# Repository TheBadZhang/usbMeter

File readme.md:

# usbMeter

简易 usb 电流表，精度 1mA，支持正负 4.0A 电流测量。

## 实物

## 更新注记

### V1.0.0

实现了最基础的电压、电流、功率的读取和显示

### V0.0.1

这个版本是最初的版本，具有我能够塞入的所有功能，结果发现嘉立创免费打样只支持0.3mm的孔，导致没有办法低价进行生产，随放弃，删除大量功能，只保留了最基本的功能，做出了 V1.0.0 版本

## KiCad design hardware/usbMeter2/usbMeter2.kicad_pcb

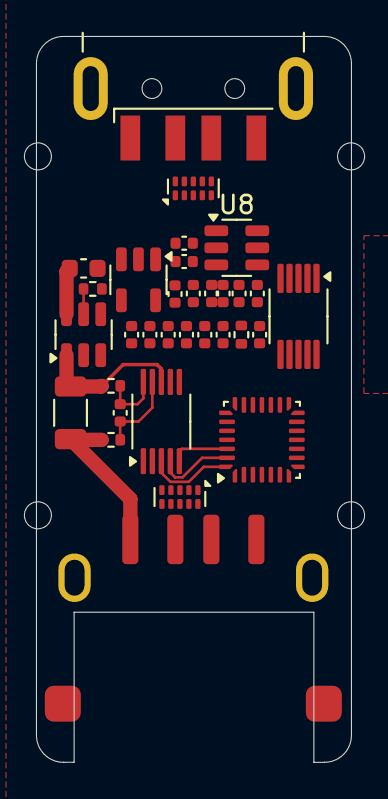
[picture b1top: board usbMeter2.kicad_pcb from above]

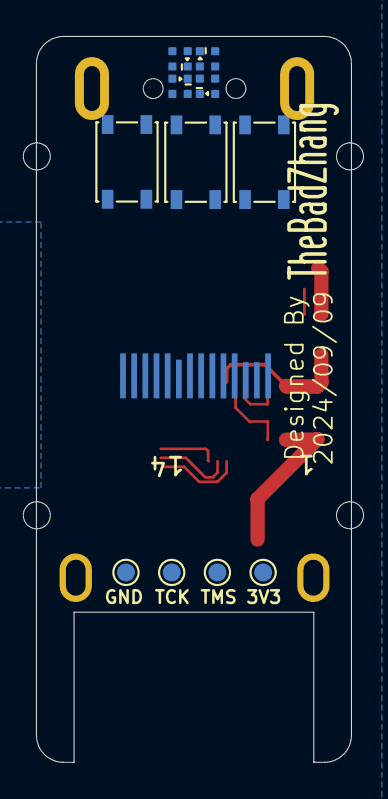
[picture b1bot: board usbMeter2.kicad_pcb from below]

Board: 2 copper layers, 17.5 x 40.3 mm, 48 parts (12 on the bottom side), 44 nets.

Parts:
C1, C20: 2.2uF; C_0402_1005Metric
C2, C5: 100nF; C_0402_1005Metric
C3, C4, C8, C18, C22: 0.1uF; C_0402_1005Metric
C6: 10uF; C_0603_1608Metric
C7, C10, C19, C21: 4.7uF; C_0402_1005Metric
C9: 22nF; C_0402_1005Metric
C16, C17: 1uF; C_0402_1005Metric
D1, D2, D3, D4: WS2812B-2020; ws2812-1010
H1, H2, H3, H4: MountingHole; mountinghold_nopad_m1.4
J1: USB_A; USB_A_CNCTech_1001-011-01101_Horizontal
J2: USB_A; C2763021
R3, R5: 68R; R_0402_1005Metric
R4: 20mR; R_1206_3216Metric
R6: 100k; R_0402_1005Metric
R12: 560K; R_0402_1005Metric
SW1, SW2, SW3: SW_Push; KEY-SMD_4P-L4.2-W3.4-P2.15-LS4.5-TL
TP1, TP2, TP3, TP4: TestPoint; TestPoint_Pad_D1.0mm
U1: STM32G031G8Ux; QFN-28_4x4mm_P0.5mm
U2, U3: TPD4E05U06DQA; USON-10_2.5x1.0mm_P0.5mm
U4: CH340E; MSOP-10_3x3mm_P0.5mm
U5: INA228; VSSOP-10_3x3mm_P0.5mm
U6: CH217K; TSOT-23-6
U7: RT9193-33GB; SOT-23-5
U8: TPS54202DDC; SOT-23-6
U9: iic_oled_12864_ssd1312_2

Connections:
+3V3: C1.1, C2.1, C3.1, C4.1, C10.2, C18.1, C19.1, TP3.1, U1.3 (VDD), U4.7 (VCC), U4.10 (V3), U5.6 (VS), U7.5 (Vout), U9.5 (VBAT), U9.8 (VDD)
+5V: C7.1, C8.1, U7.1 (Vin), U7.3 (EN)
/CH217_FLAG: U1.14 (PB0), U6.3 (FLAG#)
/D2+: J1.3 (D+), U3.4 (D2+), U3.7 (NC), U4.1 (UD+)
/D2-: J1.2 (D-), U3.2 (D1-), U3.9 (NC), U4.2 (UD-)
/D+: J2.3 (D+), U2.4 (D2+), U2.7 (NC)
/D-: J2.2 (D-), U2.5 (D2-), U2.6 (NC)
/KEY1: SW1.2, U1.23 (PB3)
/KEY2: SW2.2, U1.24 (PB4)
/NRST: SW3.2, U1.5 (PF2)
/OLED_RST: U1.22 (PA15), U9.9 (RES#)
/SCL1: U1.26 (PB6), U5.5 (SCL)
/SCL2: U1.18 (PA11/PA9), U9.10 (SCL)
/SDA1: U1.27 (PB7), U5.4 (SDA)
/SDA2: U1.19 (PA12/PA10), U9.11 (SDA)
/SYS_SWCLK: TP2.1, U1.21 (PA14)
/SYS_SWDIO: TP1.1, U1.20 (PA13)
/UART_RX: U1.9 (PA3), U4.8 (TXD)
/UART_TX: U1.8 (PA2), U4.9 (RXD)
/WS2812_OUT: D1.3 (DIN), U1.25 (PB5)
/ch217x/VOUT: R3.1, R4.1, U5.8 (Vbus), U6.1 (VOUT)
/~CH217_EN: U1.13 (PA7), U6.4 (EN#)
/~INA226_ALERT: U1.28 (PB8), U5.3 (~Alert)
GND: C1.2, C2.2, C3.2, C4.2, C6.1, C7.2, C8.2, C9.2, C10.1, C18.2, C19.2, C20.2, C21.2, C22.2, D1.2 (VSS), D2.2 (VSS), D3.2 (VSS), D4.2 (VSS), J1.4 (GND), J1.5 (Shield), J2.4 (GND), J2.5 (Shield), R6.1, R12.1, SW1.1, SW2.1, SW3.1, TP4.1, U1.4 (VSS), U2.3 (GND), U2.8 (GND), U3.3 (GND), U3.8 (GND), U4.3 (GND), U5.1 (A1), U5.2 (A0), U5.7 (GND), U6.2 (GND), U7.2 (GND), U8.1 (GND), U9.7 (VSS)
unnamed: D1.1 (DOUT), D2.3 (DIN)
unnamed: D2.1 (DOUT), D3.3 (DIN)
unnamed: D3.1 (DOUT), D4.3 (DIN)
unnamed: U2.1 (D1+), U2.10 (NC)
unnamed: U2.2 (D1-), U2.9 (NC)
unnamed: U3.1 (D1+), U3.10 (NC)
unnamed: U3.5 (D2-), U3.6 (NC)
unnamed: C5.1, R3.2, U5.10 (Vin+)
unnamed: C5.2, R5.2, U5.9 (Vin-)
unnamed: R6.2, U6.5 (ISET)
unnamed: C9.1, U7.4 (BP)
unnamed: C17.1, U9.4 (C1N)
unnamed: C17.2, U9.3 (C1P)
unnamed: C16.1, U9.2 (C2N)
unnamed: C16.2, U9.1 (C2P)
unnamed: R12.2, U9.12 (IREF)
unnamed: C21.1, C22.1, U9.14 (VCC)
unnamed: C20.1, U9.13 (VCOMH)
VBUS: C6.2, D1.4 (VDD), D2.4 (VDD), D3.4 (VDD), D4.4 (VDD), J1.1 (VBUS), U6.6 (VIN), U8.3 (VIN)
VBUS2: J2.1 (VBUS), R4.2, R5.1

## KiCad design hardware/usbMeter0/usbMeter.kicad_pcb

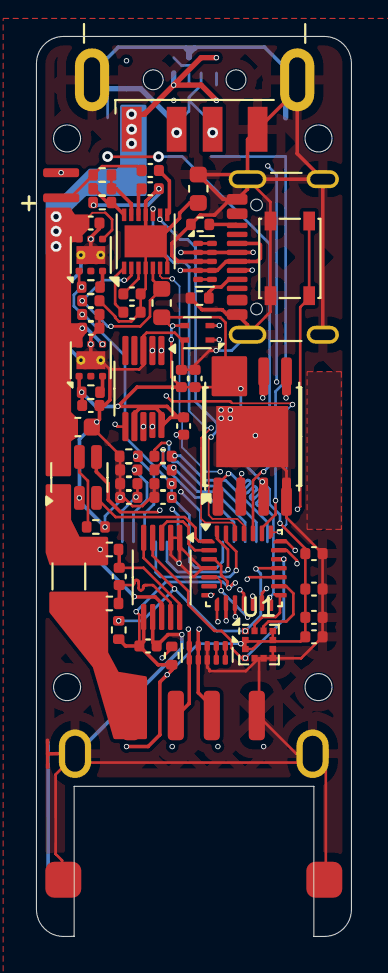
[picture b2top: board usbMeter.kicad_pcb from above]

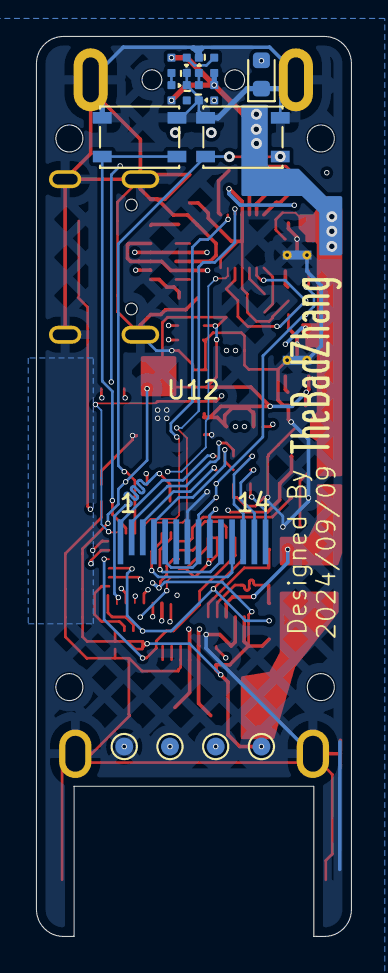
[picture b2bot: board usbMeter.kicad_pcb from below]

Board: 4 copper layers, 17.5 x 50.0 mm, 76 parts (12 on the bottom side), 66 nets.

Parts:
C1, C2, C9, C13: 0.1uF; C_0402_1005Metric
C3, C15, C16, C21, C22, C24, C25: 100nF; C_0402_1005Metric
C4, C19, C23: 10uF; C_0402_1005Metric
C5, C10, C12, C20: 4.7uF; C_0402_1005Metric
C6: 10uF; C_0603_1608Metric
C7, C8, C14: 1uF; C_0402_1005Metric
C11, C18, C26: 2.2uF; C_0402_1005Metric
C17: 470nF; C_0402_1005Metric
D1: LED; LED_0603_1608Metric
D2, D3, D4, D5: WS2812B-2020; ws2812-1010
H1, H2, H3, H4: MountingHole; mountinghold_nopad_m1.4
J1: USB_A; USB_A_CNCTech_1001-011-01101_Horizontal
J2: USB_A; C2763021
J3: USB_C_Receptacle_USB2.0_16P; USB_C_Receptacle_GCT_USB4105-xx-A_16P_TopMnt_Horizontal
L1, L2: FerriteBead_0603_1.5A; L_0603_1608Metric
MK1: Microphone_Condenser; MIC4015P_2
R1, R2, R6, R12, R13, R14: 5.1k; R_0402_1005Metric
R3, R5: 68R; R_0402_1005Metric
R4: 20mR; R_1206_3216Metric
R7, R11: 100k; R_0402_1005Metric
R8: 560K; R_0402_1005Metric
R9: 150k; R_0402_1005Metric
R10: 2.2k; R_0402_1005Metric
SW3, SW4, SW5: SW_Push; KEY-SMD_4P-L4.2-W3.4-P2.15-LS4.5-TL
TP1, TP2, TP3, TP4: TestPoint; TestPoint_Pad_D1.0mm
U1: LIS2HH12; LGA-12_2x2mm_P0.5mm
U2: STM32G031G8Ux; QFN-28_4x4mm_P0.5mm
U3, U8: TPD4E05U06DQA; USON-10_2.5x1.0mm_P0.5mm
U4: SHT4x; Sensirion_DFN-4_1.5x1.5mm_P0.8mm_SHT4x_NoCentralPad
U5: W25Q32JVZP; WSON-8-1EP_6x5mm_P1.27mm_EP3.4x4mm
U6: W25Q128JVS; SOIC-8_5.23x5.23mm_P1.27mm
U7: CH340E; MSOP-10_3x3mm_P0.5mm
U9: INA228; VSSOP-10_3x3mm_P0.5mm
U10, U14: LP5912-3.3DRV; WSON-6-1EP_2x2mm_P0.65mm_EP1x1.6mm_ThermalVias
U11: CH217K; TSOT-23-6
U12: iic_oled_12864_ssd1312_2
U13: MAX9814; DFN-14-1EP_3x3mm_P0.4mm_EP1.78x2.35mm

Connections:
+3V3: C1.1, C2.1, C5.1, C21.1, C22.1, C23.1, C24.1, C25.1, C26.1, L1.1, R6.1, R13.1, R14.1, TP2.1, U1.2 (~CS), U1.3 (SA0/SDO), U1.9 (Vdd), U1.10 (Vdd_IO), U2.3 (VDD), U4.3 (VDD), U5.3 (IO2), U5.7 (IO3), U5.8 (VCC), U6.3 (IO2), U6.7 (IO3), U6.8 (VCC), U7.7 (VCC), U7.10 (V3), U9.6 (VS), U10.1 (OUT)
+5V: J2.1 (VBUS), R4.2, R5.1
/ACC_INT1: U1.12 (INT1), U2.15 (PB1)
/ACC_INT2: U1.11 (INT2), U2.16 (PA8)
/ADC_IN5: U2.11 (PA5), U13.6 (MICOUT)
/A/R: U2.25 (PB5), U13.9 (A/R)
/CH217_FLAG: U2.1 (PC14), U11.3 (FLAG#)
/D2+: J3.A6 (D+), J3.B6 (D+), U7.1 (UD+), U8.4 (D2+), U8.7 (NC)
/D2-: J3.A7 (D-), J3.B7 (D-), U7.2 (UD-), U8.2 (D1-), U8.9 (NC)
/D+: J1.3 (D+), J2.3 (D+), U3.4 (D2+), U3.7 (NC)
/D-: J1.2 (D-), J2.2 (D-), U3.5 (D2-), U3.6 (NC)
/Gain: U2.26 (PB6), U13.10 (GAIN)
/KEY1: SW3.2, U2.23 (PB3)
/KEY2: SW4.2, U2.24 (PB4)
/MAX9814/B3v3: C14.1, L1.2, U13.2 (~SHDN), U13.5 (VDD)
/MAX9814/BGND: C14.2, C16.2, C17.2, C18.2, L2.2, MK1.1 (-), R11.1, U13.4 (GND), U13.7 (GND), U13.11 (GND), U13.15 (GND)
/MAX9814/BIAS: C17.1, U13.12 (BIAS)
/MAX9814/CT: C16.1, U13.1 (CT)
/MAX9814/MICBIAS: R9.1, R10.2, U13.13 (MICBIAS)
/MAX9814/MICIN: C15.1, U13.8 (MICIN)
/MAX9814/TH: R9.2, R11.2, U13.14 (TH)
/NRST: SW5.2, U2.5 (PF2)
/OLED_RST: U2.22 (PA15), U12.9 (RES#)
/OLED_VCC: C9.1, C10.1, C20.1, R12.1, U12.5 (VBAT), U12.8 (VDD), U14.1 (OUT)
/SCL: U2.28 (PB8), U12.10 (SCL)
/SCL2: R14.2, U1.1 (SCL/SPC), U2.18 (PA11/PA9), U4.2 (SCL), U9.5 (SCL)
/SDA: U2.27 (PB7), U12.11 (SDA)
/SDA2: R13.2, U1.4 (SDA/SDI), U2.19 (PA12/PA10), U4.1 (SDA), U9.4 (SDA)
/SPI_CLK: U2.7 (PA1), U5.6 (CLK), U6.6 (CLK)
/SPI_MISO: U2.12 (PA6), U5.2 (DO(IO1)), U6.2 (DO(IO1))
/SPI_MOSI: U2.13 (PA7), U5.5 (DI(IO0)), U6.5 (DI(IO0))
/SPI_NSS: U2.14 (PB0), U5.1 (~CS), U6.1 (~CS)
/SYS_SWCLK: TP3.1, U2.21 (PA14)
/SYS_SWDIO: TP4.1, U2.20 (PA13)
/UART_RX: U2.9 (PA3), U7.8 (TXD)
/UART_TX: U2.8 (PA2), U7.9 (RXD)
/WS2812_OUT: D2.3 (DIN), U2.10 (PA4)
/ch217x/VOUT: R3.1, R4.1, U9.8 (Vbus), U11.1 (VOUT)
/~CH217_EN: U2.17 (PC6), U11.4 (EN#)
/~INA226_ALERT: U2.2 (PC15), U9.3 (~Alert)
GND: C1.2, C2.2, C4.2, C5.2, C6.1, C9.2, C10.2, C11.2, C12.2, C13.2, C19.2, C20.2, C21.2, C22.2, C23.2, C24.2, C25.2, C26.2, D1.1 (K), D2.2 (VSS), D3.2 (VSS), D4.2 (VSS), D5.2 (VSS), J1.4 (GND), J1.5 (Shield), J2.4 (GND), J2.5 (Shield), J3.A1 (GND), J3.A12 (GND), J3.B1 (GND), J3.B12 (GND), J3.S1 (SHIELD), L2.1, R1.2, R2.2, R7.1, R8.1, SW3.1, SW4.1, SW5.1, TP1.1, U1.5 (RES), U1.6 (GND), U1.7 (GND), U1.8 (GND), U2.4 (VSS), U3.3 (GND), U3.8 (GND), U4.4 (VSS), U5.4 (GND), U5.9 (EP), U6.4 (GND), U7.3 (GND), U8.3 (GND), U8.8 (GND), U9.1 (A1), U9.2 (A0), U9.7 (GND), U10.5 (GND), U10.7 (EP), U11.2 (GND), U12.7 (VSS), U14.5 (GND), U14.7 (EP)
unnamed: D1.2 (A), U7.6 (TNOW)
unnamed: D2.1 (DOUT), D3.3 (DIN)
unnamed: D3.1 (DOUT), D4.3 (DIN)
unnamed: D4.1 (DOUT), D5.3 (DIN)
unnamed: J3.A5 (CC1), R2.1
unnamed: J3.B5 (CC2), R1.1
unnamed: C15.2, MK1.2 (+), R10.1
unnamed: U3.1 (D1+), U3.10 (NC)
unnamed: U3.2 (D1-), U3.9 (NC)
unnamed: U8.1 (D1+), U8.10 (NC)
unnamed: U8.5 (D2-), U8.6 (NC)
unnamed: C3.1, R3.2, U9.10 (Vin+)
unnamed: C3.2, R5.2, U9.9 (Vin-)
unnamed: R6.2, U10.3 (PG)
unnamed: R7.2, U11.5 (ISET)
unnamed: C8.1, U12.4 (C1N)
unnamed: C8.2, U12.3 (C1P)
unnamed: C7.1, U12.2 (C2N)
unnamed: C7.2, U12.1 (C2P)
unnamed: R8.2, U12.12 (IREF)
unnamed: C12.1, C13.1, U12.14 (VCC)
unnamed: C11.1, U12.13 (VCOMH)
unnamed: C18.1, U13.3 (CG)
unnamed: R12.2, U14.3 (PG)
VBUS: C4.1, C6.2, C19.1, D2.4 (VDD), D3.4 (VDD), D4.4 (VDD), D5.4 (VDD), J1.1 (VBUS), U10.4 (EN), U10.6 (IN), U11.6 (VIN), U14.4 (EN), U14.6 (IN)

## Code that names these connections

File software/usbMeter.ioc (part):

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Mcu.Name=STM32G031G(4-6-8)Ux
Mcu.Package=UFQFPN28
Mcu.UserName=STM32G031G8Ux
PA1.Mode=TX_Only_Simplex_Unidirect_Master
PA1.Signal=SPI1_SCK
PA11\ [PA9].GPIOParameters=GPIO_Pu
PA11\ [PA9].GPIO_Pu=GPIO_PULLUP
PA11\ [PA9].Mode=I2C
PA11\ [PA9].Signal=I2C2_SCL
PA12\ [PA10].GPIOParameters=GPIO_Pu
PA12\ [PA10].GPIO_Pu=GPIO_PULLUP
PA12\ [PA10].Mode=I2C
PA12\ [PA10].Signal=I2C2_SDA
PA13.Mode=Serial_Wire
PA13.Signal=SYS_SWDIO
PA14-BOOT0.Mode=Serial_Wire
PA14-BOOT0.Signal=SYS_SWCLK
PA15.GPIOParameters=GPIO_Label
PA15.GPIO_Label=OLED_RST
PA15.Signal=GPIO_Output
PA2.Mode=Asynchronous
PA2.Signal=USART2_TX
PA3.Mode=Asynchronous
PA3.Signal=USART2_RX
PA7.GPIOParameters=GPIO_Label
PA7.GPIO_Label=CH217_EN
PA7.Signal=GPIO_Output
PB0.GPIOParameters=GPIO_Label
PB0.GPIO_Label=CH217_FLAG
PB0.Signal=GPXTI0
PB3.GPIOParameters=GPIO_PuPd,GPIO_Label
PB3.GPIO_Label=KEY1
PB3.GPIO_PuPd=GPIO_PULLUP
PB3.Signal=GPIO_Input
PB4.GPIOParameters=GPIO_PuPd,GPIO_Label
PB4.GPIO_Label=KEY2
PB4.GPIO_PuPd=GPIO_PULLUP
PB4.Signal=GPIO_Input
PB5.Mode=TX_Only_Simplex_Unidirect_Master
PB5.Signal=SPI1_MOSI
PB6.GPIOParameters=GPIO_FM6,GPIO_Pu
PB6.GPIO_FM6=SYSCFG_FASTMODEPLUS_PB6
PB6.GPIO_Pu=GPIO_PULLUP
PB6.Mode=I2C
PB6.Signal=I2C1_SCL
PB7.GPIOParameters=GPIO_Pu,GPIO_FM7
PB7.GPIO_FM7=SYSCFG_FASTMODEPLUS_PB7
PB7.GPIO_Pu=GPIO_PULLUP
PB7.Mode=I2C
PB7.Signal=I2C1_SDA
PC6.GPIOParameters=GPIO_Label
PC6.GPIO_Label=INA226_ALERT
PC6.Signal=GPXTI6
RCC.HSE_VALUE=8000000
RCC.SYSCLKFreq_VALUE=64000000
RCC.SYSCLKSource=RCC_SYSCLKSOURCE_PLLCLK
board=custom

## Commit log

2024-09-22 usbMeter 软件部分，基本功能开发进度95%
2024-09-22 usbMeter 硬件部分，V1.0设计完成
    还有一些可以优化的部分，之后将产生后续的版本，此版本功能一切正常
2024-09-22 更新 readme 文件
2024-09-22 .gitignore
2024-09-22 根据不同的硬件版本对硬件进行分类
2024-09-22 添加了对旧版本的描述
2024-09-22 开始计划 V2.0.0 的开发
2024-09-22 更新一张效果图
2024-09-22 优化了 ina226 相关的代码，解耦优化
    在此处遇到一个很奇怪的问题，current变量时不时打印的时候会变成一个很大的值，但是并不知道是为什么，计算了current_ls*2^15并不会超过1000，但是它得到了一个很大的值，2600左右，后来想在它显示这个值之前打印出来具体的数值，结果问题就消失了，看来是额外的对current变量的操作导致了问题，把它设置成 volatile 并没有什么效果，后来在编译选项的优化选项从Og改成了O2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
2024-09-22 上一个commit的部分解释
    看了一下，Og选项把xprintf库的体积优化了50%，估计在这丢失了很多奇怪的东西
2024-09-22 验证下来xprintf这个库还是不够稳健
    最终还是更换为标准库，相比xprintf库，格式化浮点数的时候，会额外增加10K code
2024-09-22 usbmeter2尝试缩减了本体的尺寸，采用dcdc+ldo供电避免typea可能存在的高压输入
2024-09-22 优化了浮点数输出的代码，增加了更多字体支持，优化了界面表现
